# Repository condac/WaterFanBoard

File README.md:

# WaterFanBoard
PCB board for temperature and fan extensions for water cooling

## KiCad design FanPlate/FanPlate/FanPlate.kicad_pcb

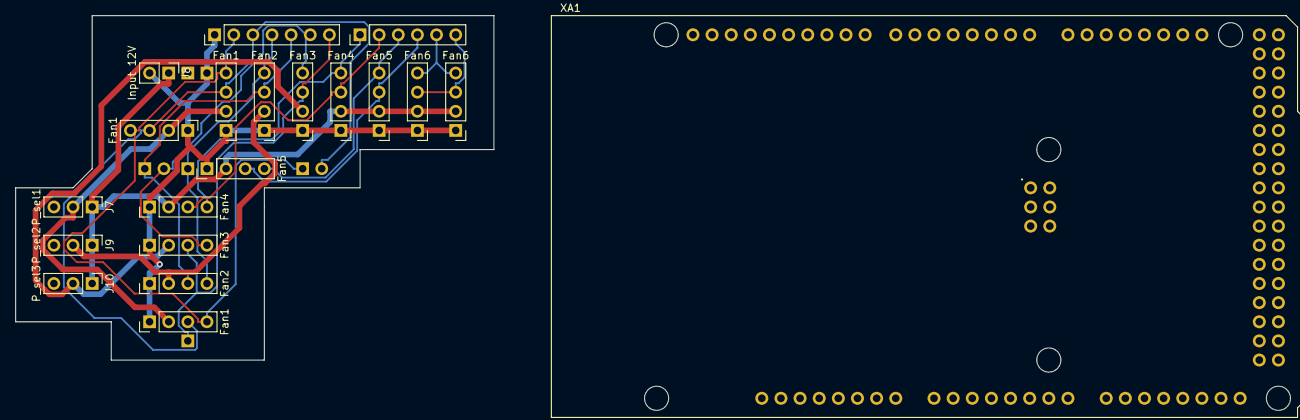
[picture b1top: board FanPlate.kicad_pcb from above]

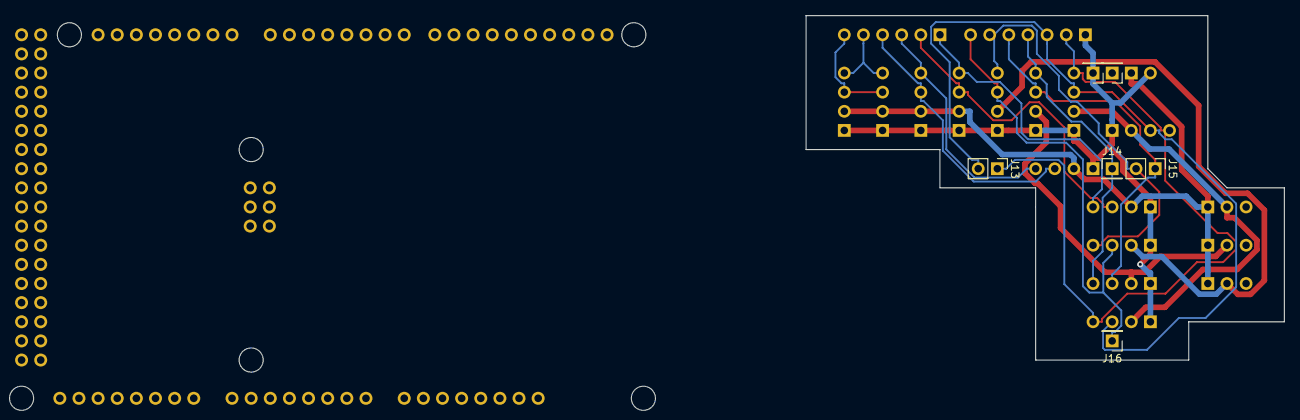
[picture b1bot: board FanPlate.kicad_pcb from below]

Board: 2 copper layers, 63.5 x 45.7 mm, 26 parts (6 on the bottom side), 17 nets.

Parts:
J1, J122, J1123: Fan1; PinHeader_1x04_P2.54mm_Vertical
J2, J22: Fan2; PinHeader_1x04_P2.54mm_Vertical
J3, J32: Fan3; PinHeader_1x04_P2.54mm_Vertical
J4, J4123: Fan4; PinHeader_1x04_P2.54mm_Vertical
J5, J5123: Fan5; PinHeader_1x04_P2.54mm_Vertical
J6, J6123: Fan6; PinHeader_1x04_P2.54mm_Vertical
J7: P_sel1; PinHeader_1x03_P2.54mm_Vertical
J8: Input 12V; PinHeader_1x02_P2.54mm_Vertical
J9: P_sel2; PinHeader_1x03_P2.54mm_Vertical
J10: P_sel3; PinHeader_1x03_P2.54mm_Vertical
J11: Arduino_P1; PinHeader_1x07_P2.54mm_Vertical
J12: Arduino_P2; PinHeader_1x06_P2.54mm_Vertical
J13: RAMPS_P1; PinHeader_1x02_P2.54mm_Vertical
J14: RAMPS_P2; PinHeader_1x01_P2.54mm_Vertical
J15: RAMPS_P3; PinHeader_1x02_P2.54mm_Vertical
J16: RAPMS_P4; PinHeader_1x01_P2.54mm_Vertical
J17: RAMPS_12v; PinHeader_1x01_P2.54mm_Vertical
J18: RAMPS_GND; PinHeader_1x01_P2.54mm_Vertical
XA1: Arduino_Mega2560_Shield

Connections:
/12V: J4.2, J5.2, J6.2, J7.1, J8.1, J9.1, J10.1, J4123.2, J5123.2, J6123.2
/FAN1: J1.3, J11.3, J13.2, J122.3, J1123.3
/FAN2: J2.3, J11.5, J15.1, J22.3
/FAN3: J3.3, J11.7, J16.1, J32.3
/FAN4: J4.3, J12.2, J4123.3
/FAN5: J5.3, J12.4, J5123.3
/FAN6: J6.3, J12.6, J6123.3
/FAN_P1: J1.2, J7.2, J122.2, J1123.2
/FAN_P2: J2.2, J9.2, J22.2
/FAN_P3: J3.2, J10.2, J32.2
/GND: J1.1, J2.1, J3.1, J4.1, J5.1, J6.1, J8.2, J11.1, J18.1, J22.1, J32.1, J122.1, J1123.1, J4123.1, J5123.1, J6123.1
/PWM1: J1.4, J11.2, J13.1, J122.4, J1123.4
/PWM2: J2.4, J11.4, J14.1, J22.4
/PWM3: J3.4, J11.6, J15.2, J32.4
/PWM4: J4.4, J12.1, J4123.4
/PWM5: J5.4, J12.3, J5123.4
/PWM6: J6.4, J12.5, J6123.4

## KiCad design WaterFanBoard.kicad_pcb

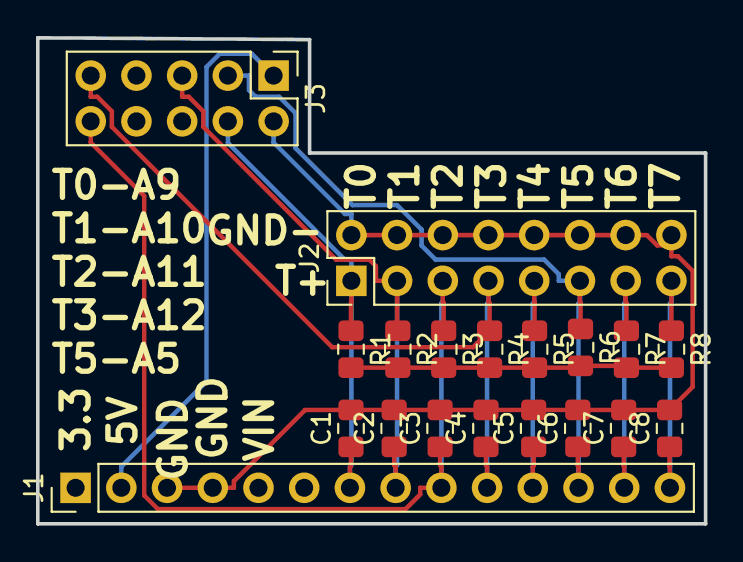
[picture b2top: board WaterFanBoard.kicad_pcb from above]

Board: 2 copper layers, 37.1 x 27.0 mm, 19 parts (0 on the bottom side), 11 nets.

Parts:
C1, C2, C3, C4, C5, C6, C7, C8: 10uF; C_0805_2012Metric_Pad1.15x1.40mm_HandSolder
J1: Conn_01x14; PinHeader_1x14_P2.54mm_Vertical
J2: Conn_02x08_Top_Bottom; PinHeader_2x08_P2.54mm_Vertical
J3: Conn_02x05_Odd_Even; PinHeader_2x05_P2.54mm_Vertical
R1, R2, R3, R4, R5, R6, R7, R8: 4.7K; R_0805_2012Metric_Pad1.15x1.40mm_HandSolder

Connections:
+5V: R1.2, R2.2, R3.2, R4.2, R5.2, R6.2, R7.2, R8.2
/5V: J1.2, J3.1
/A0: C1.1, J1.7, J2.1, J3.4, R1.1
/A1: C2.1, J1.8, J2.3, J3.5, R2.1
/A4: C5.1, J1.11, J2.9, R5.1
/A5: C6.1, J1.12, J2.11, J3.3, R6.1
/A6: C7.1, J1.13, J2.13, R7.1
/A7: C8.1, J1.14, J2.15, R8.1
/A11: C3.1, J1.9, J2.5, J3.10, R3.1
/A12: C4.1, J1.10, J2.7, J3.9, R4.1
GND: C1.2, C2.2, C3.2, C4.2, C5.2, C6.2, C7.2, C8.2, J1.3, J1.4, J2.2, J2.4, J2.6, J2.8, J2.10, J2.12, J2.14, J2.16, J3.2

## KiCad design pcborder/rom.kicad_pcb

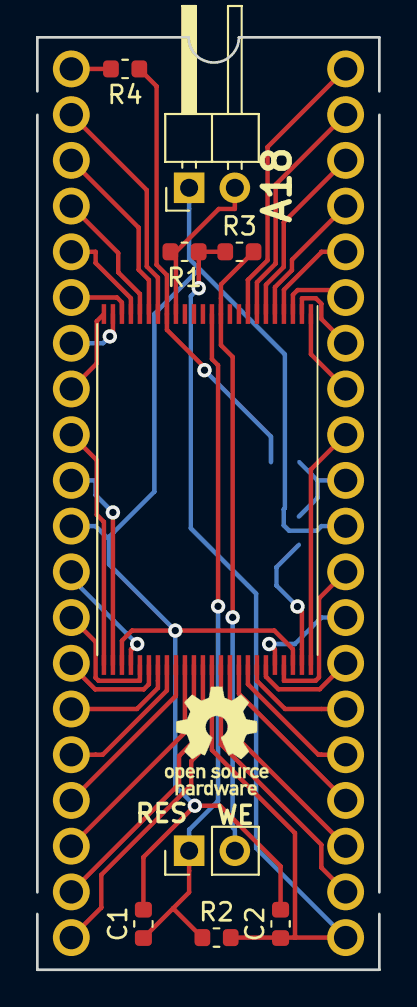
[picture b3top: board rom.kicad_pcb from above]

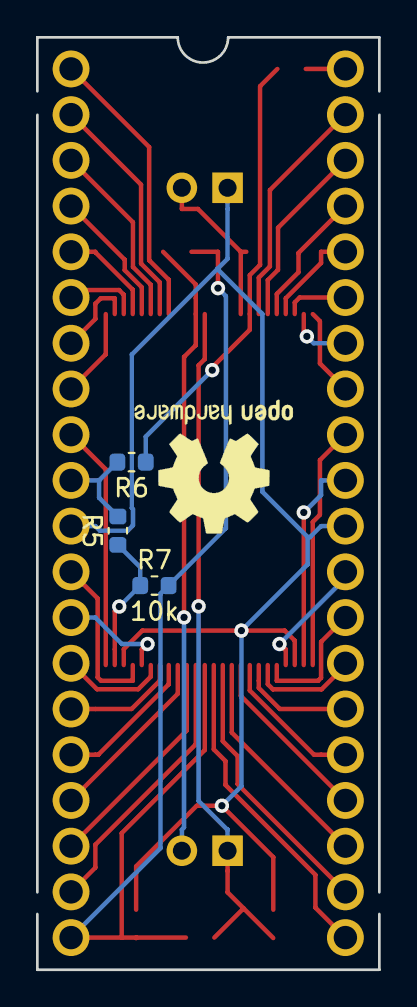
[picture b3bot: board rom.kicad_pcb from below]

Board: 2 copper layers, 19.0 x 51.8 mm, 13 parts (3 on the bottom side), 44 nets.

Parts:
C1, C2: 0.1uF; C_0603_1608Metric
J1: Conn_01x02; PinHeader_1x02_P2.54mm_Horizontal
J2: Conn_01x02; PinHeader_1x02_P2.54mm_Vertical
R1, R2, R3: 10K; R_0603_1608Metric
R4, R5, R6: 0; R_0603_1608Metric
R7: 10k; R_0603_1608Metric
U1: 27C4002
U2: 29F800; TSOP-I-48_18.4x12mm_P0.5mm

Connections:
/P1_1: R4.2, U1.1
/P1_2: R4.1, R6.1, U2.17
/P2: U1.2, U2.18
/P3: U1.3, U2.19
/P4: U1.4, U2.20
/P5: U1.5, U2.21
/P6: U1.6, U2.22
/P7: U1.7, U2.23
/P8: U1.8, U2.24
/P9: U1.9, U2.25
/P10: U1.10, U2.26
/P12: U1.12, U2.28
/P13: U1.13, U2.29
/P14: U1.14, U2.30
/P15: U1.15, U2.31
/P16: U1.16, U2.32
/P17: U1.17, U2.33
/P18: U1.18, U2.34
/P19: U1.19, U2.35
/P20: U1.20, U2.36
/P22: U1.22, U2.38
/P23: U1.23, U2.39
/P24: U1.24, U2.40
/P25: U1.25, U2.41
/P26: U1.26, U2.42
/P27: U1.27, U2.43
/P28: U1.28, U2.44
/P29: U1.29, U2.45
/P31_1: R5.2, R6.2, U1.31
/P31_2: R5.1, R7.1, U2.47
/P32: U1.32, U2.48
/P33: U1.33, U2.1
/P34: U1.34, U2.2
/P35: U1.35, U2.3
/P36: U1.36, U2.4
/P37: U1.37, U2.5
/P38: U1.38, U2.6
/P39: U1.39, U2.7
/P40: U1.40, U2.8
/P_A18: J1.2, R1.2, U2.16
/P_RST: C1.1, J2.1, R2.1, U2.12
/P_WE: J2.2, R3.2, U2.11
VCC: C2.1, R1.1, R2.2, R3.1, R7.2, U1.21, U2.37
VSS: C1.2, C2.2, J1.1, U1.11, U1.30, U2.27, U2.46

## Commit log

2018-10-16 First temperature board prototype
2018-10-26 Fanplate
